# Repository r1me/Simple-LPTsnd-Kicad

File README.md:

# Simple-LPTsnd
Covox Speech Thing Clone / DAC for LPT Port

Added SMD 1206 revision made in Kicad 6

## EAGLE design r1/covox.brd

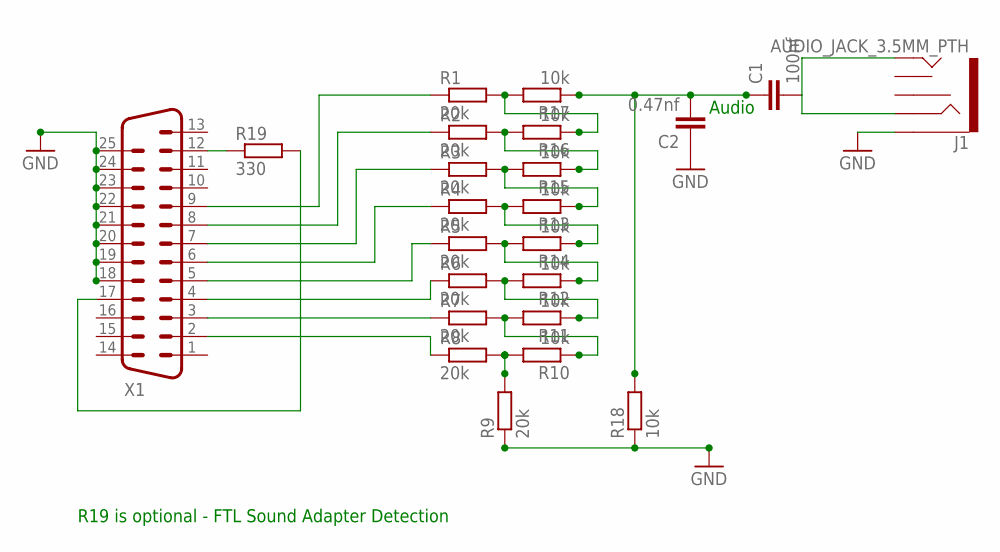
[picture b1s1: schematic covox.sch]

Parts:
C1: 100nf; C2.5-2
C2: 0.47nf; C2.5-2
J1: AUDIO_JACK_3.5MM_PTH; AUDIO-JACK
R1, R2, R3, R4, R5, R6, R7, R8, R9: 20k; 0204/7
R10, R11, R12, R13, R14, R15, R16, R17, R18: 10k; 0204/7
R19: 330; 0204/7
X1: M25HP

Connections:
GND: C2.1, J1.SLEEVE, R9.1, R18.1, X1.18, X1.19, X1.20, X1.21, X1.22, X1.23, X1.24, X1.25
unnamed: R8.2, R9.2, R10.2
unnamed: R7.2, R10.1, R11.2
unnamed: R6.2, R11.1, R12.2
unnamed: R4.2, R13.2, R14.1
unnamed: C1.2, J1.RING, J1.TIP
unnamed: R3.2, R13.1, R15.2
unnamed: R2.2, R15.1, R16.2
unnamed: R1.2, R16.1, R17.2
unnamed: R8.1, X1.2
unnamed: R7.1, X1.3
unnamed: C1.1, C2.2, R17.1, R18.2
unnamed: R6.1, X1.4
unnamed: R5.1, X1.5
unnamed: R4.1, X1.6
unnamed: R3.1, X1.7
unnamed: R2.1, X1.8
unnamed: R5.2, R12.1, R14.2
unnamed: R1.1, X1.9
unnamed: R19.2, X1.17
unnamed: R19.1, X1.12

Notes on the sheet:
Audio
R19 is optional - FTL Sound Adapter Detection

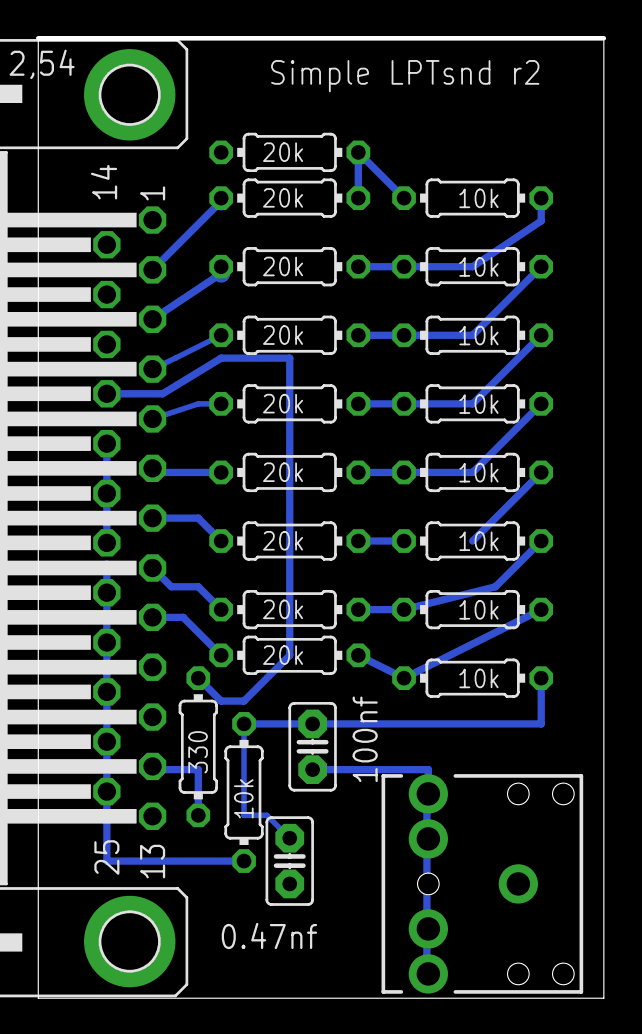
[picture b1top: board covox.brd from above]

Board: 2 copper layers, 31.4 x 53.2 mm, 23 parts (0 on the bottom side), 21 nets.

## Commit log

2020-10-04 Create revision 0
2020-10-04 Add files via upload
    Eagle CAD Files for Simple LPTsnd r0
2020-10-04 Create revision 2
2021-02-21 Create LICENSE
2022-09-15 Added SMD 1206 revision made in Kicad 6
2022-09-15 Kicad render

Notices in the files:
parts and their libraries:
SparkFun-Connectors: Licensing: Creative Commons ShareAlike 4.0 International - https://creativecommons.org/licenses/by-sa/4.0
